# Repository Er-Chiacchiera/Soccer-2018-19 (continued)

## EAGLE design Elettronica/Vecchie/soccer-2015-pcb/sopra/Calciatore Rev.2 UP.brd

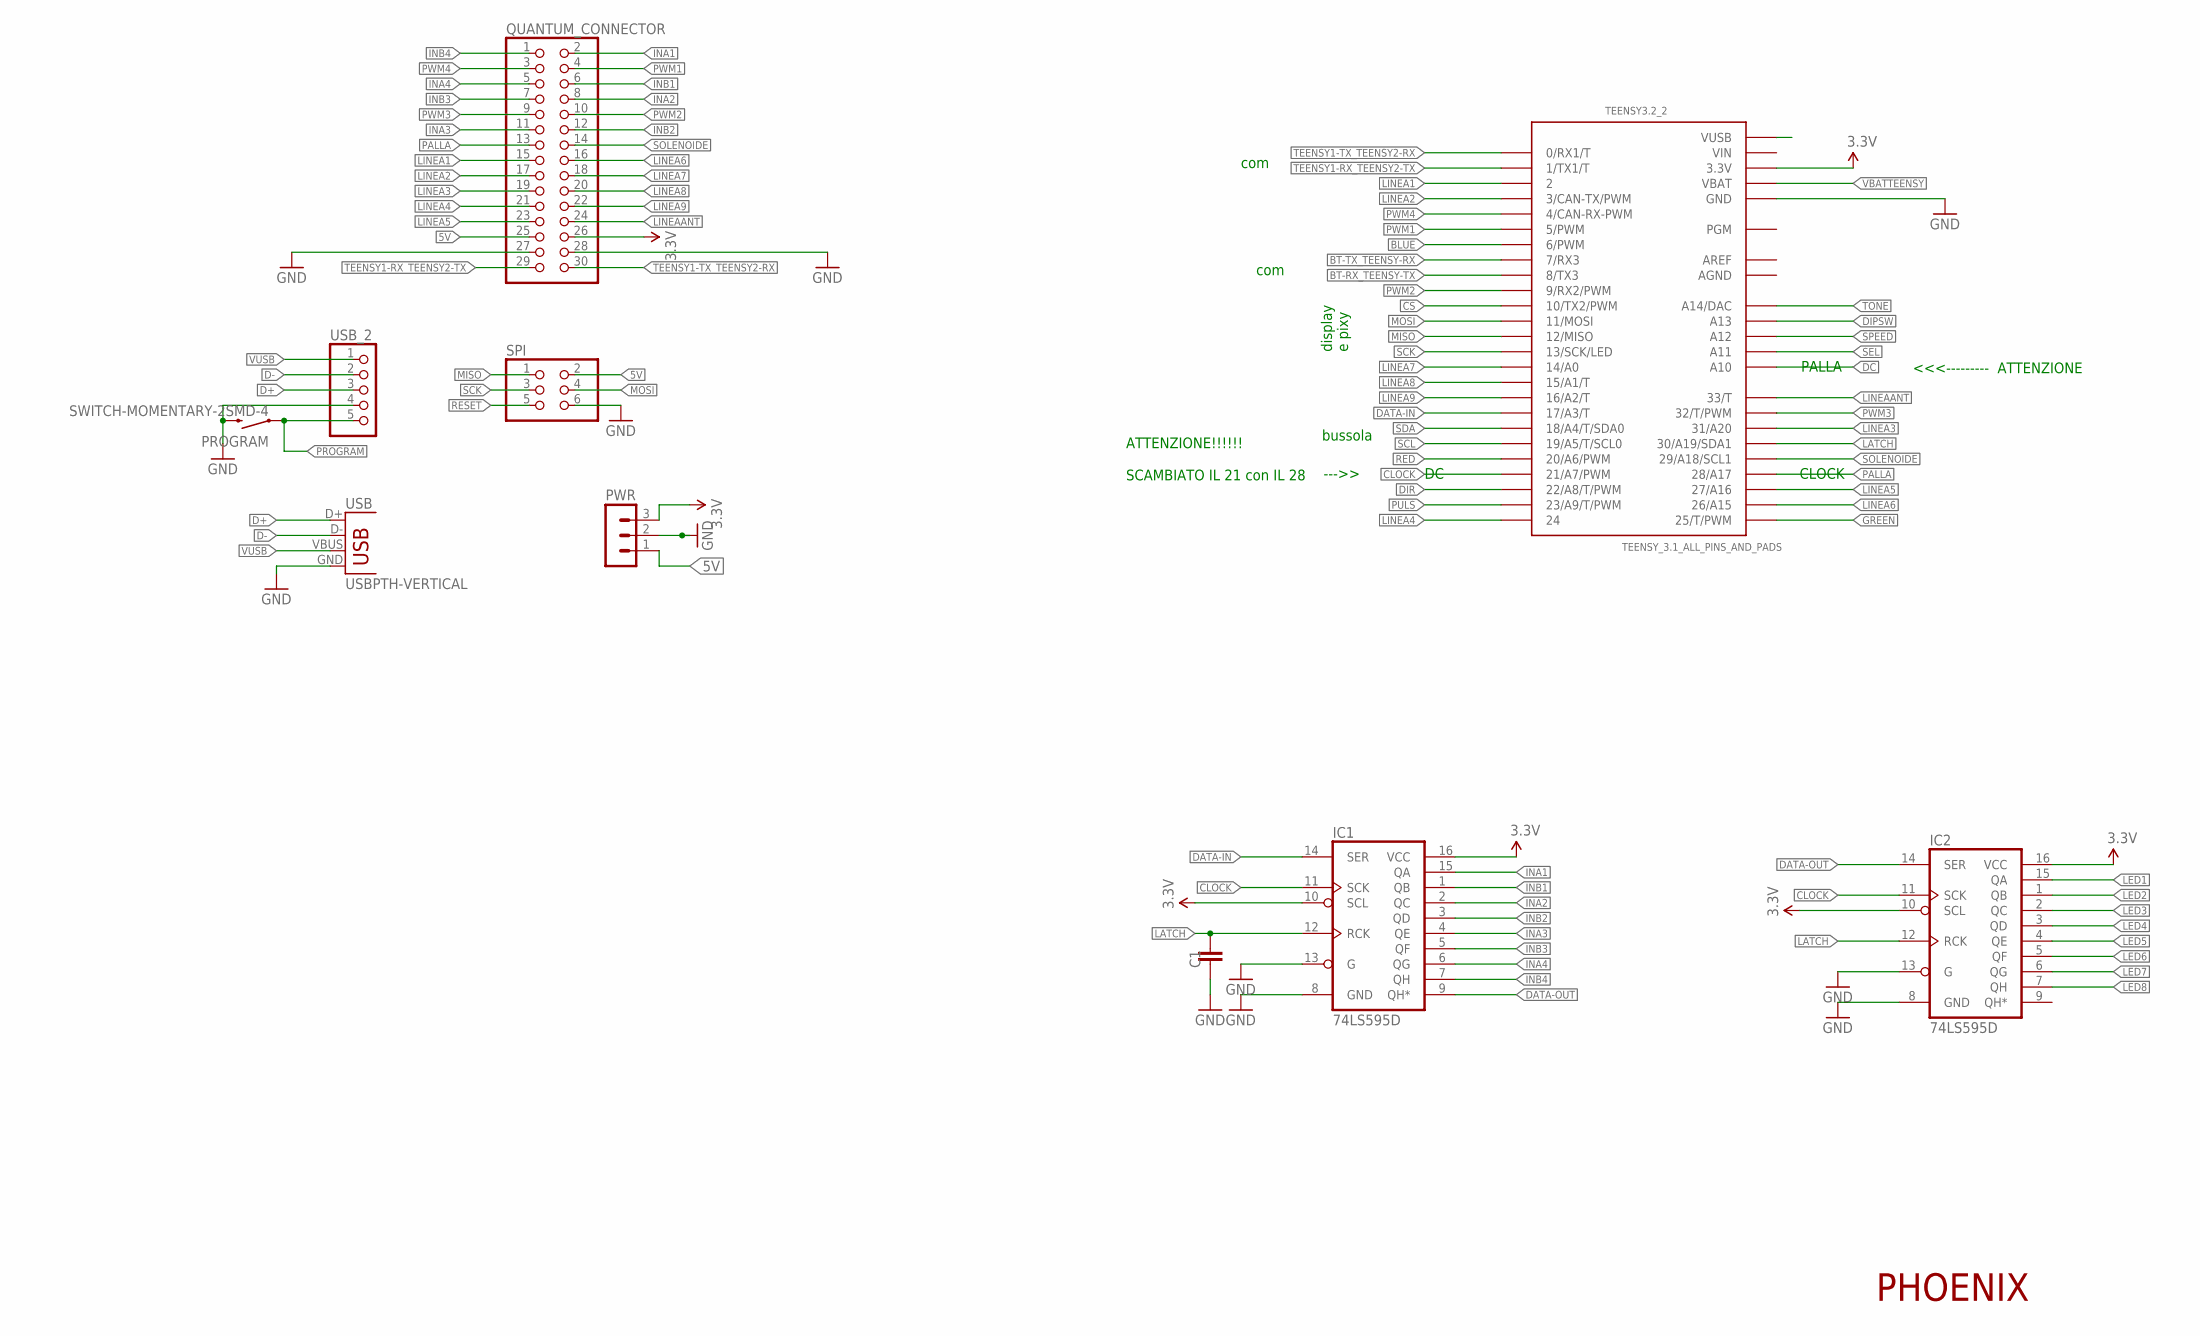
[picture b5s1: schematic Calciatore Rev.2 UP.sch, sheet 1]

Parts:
C1: C-EUC1206; C1206
IC1, IC2: 74LS595D; SO16
PROGRAM: SWITCH-MOMENTARY-2SMD-4; TACTILE_SWITCH_TALL
PWR: MA03-1
QUANTUM_CONNECTOR: PINHD-2X15; 2X15
SPI: PINHD-2X3; 2X03
TEENSY3.2_2: TEENSY_3.1_ALL_PINS_AND_PADS; TEENSY3_ALL_PINS_&_PADS
USB: USBPTH-VERTICAL; USB-B-PTH-VERTICAL
USB_2: PINHD-1X5; 1X05

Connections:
3.3V: IC1.10 (SCL), IC1.16 (VCC), IC2.10 (SCL), IC2.16 (VCC), PWR.3, QUANTUM_CONNECTOR.26, TEENSY3.2_2.3.3V, TEENSY3.2_2.3.3V1 (3.3V), TEENSY3.2_2.3.3V2 (3.3V); also elsewhere on the board
5V: PWR.1, QUANTUM_CONNECTOR.25, SPI.2; also elsewhere on the board
AGND: TEENSY3.2_2.AGND
AREF: TEENSY3.2_2.AREF
BLUE: TEENSY3.2_2.6 (6/PWM); also elsewhere on the board
BT-RX_TEENSY-TX: TEENSY3.2_2.8 (8/TX3); also elsewhere on the board
BT-TX_TEENSY-RX: TEENSY3.2_2.7 (7/RX3); also elsewhere on the board
CLOCK: IC1.11 (SCK), IC2.11 (SCK), TEENSY3.2_2.21/A7 (21/A7/PWM)
CS: TEENSY3.2_2.10 (10/TX2/PWM); also elsewhere on the board
D+: USB.D+, USB_2.3
D-: USB.D-, USB_2.2
DATA-IN: IC1.14 (SER), TEENSY3.2_2.17/A3 (17/A3/T)
DATA-OUT: IC1.9 (QH*), IC2.14 (SER)
DC: TEENSY3.2_2.A10; also elsewhere on the board
DIPSW: TEENSY3.2_2.A13; also elsewhere on the board
DIR: TEENSY3.2_2.22/A8 (22/A8/T/PWM); also elsewhere on the board
GND: C1.1, IC1.8 (GND), IC1.13 (G), IC2.8 (GND), IC2.13 (G), PROGRAM.B2 (2), PWR.2, QUANTUM_CONNECTOR.27, QUANTUM_CONNECTOR.28, SPI.6, TEENSY3.2_2.GND, TEENSY3.2_2.GND1 (GND), TEENSY3.2_2.GND2 (GND), USB.GND, USB_2.4; also elsewhere on the board
GREEN: TEENSY3.2_2.25 (25/T/PWM); also elsewhere on the board
INA1: IC1.15 (QA), QUANTUM_CONNECTOR.2
INA2: IC1.2 (QC), QUANTUM_CONNECTOR.8
INA3: IC1.4 (QE), QUANTUM_CONNECTOR.11
INA4: IC1.6 (QG), QUANTUM_CONNECTOR.5
INB1: IC1.1 (QB), QUANTUM_CONNECTOR.6
INB2: IC1.3 (QD), QUANTUM_CONNECTOR.12
INB3: IC1.5 (QF), QUANTUM_CONNECTOR.7
INB4: IC1.7 (QH), QUANTUM_CONNECTOR.1
LATCH: C1.2, IC1.12 (RCK), IC2.12 (RCK), TEENSY3.2_2.30 (30/A19/SDA1)
LED1: IC2.15 (QA); also elsewhere on the board
LED2: IC2.1 (QB); also elsewhere on the board
LED3: IC2.2 (QC); also elsewhere on the board
LED4: IC2.3 (QD); also elsewhere on the board
LED5: IC2.4 (QE); also elsewhere on the board
LED6: IC2.5 (QF); also elsewhere on the board
LED7: IC2.6 (QG); also elsewhere on the board
LED8: IC2.7 (QH); also elsewhere on the board
LINEA1: QUANTUM_CONNECTOR.15, TEENSY3.2_2.2
LINEA2: QUANTUM_CONNECTOR.17, TEENSY3.2_2.3 (3/CAN-TX/PWM)
LINEA3: QUANTUM_CONNECTOR.19, TEENSY3.2_2.31 (31/A20)
LINEA4: QUANTUM_CONNECTOR.21, TEENSY3.2_2.24
LINEA5: QUANTUM_CONNECTOR.23, TEENSY3.2_2.27 (27/A16)
LINEA6: QUANTUM_CONNECTOR.16, TEENSY3.2_2.26 (26/A15)
LINEA7: QUANTUM_CONNECTOR.18, TEENSY3.2_2.14/A0
LINEA8: QUANTUM_CONNECTOR.20, TEENSY3.2_2.15/A1 (15/A1/T)
LINEA9: QUANTUM_CONNECTOR.22, TEENSY3.2_2.16/A2 (16/A2/T)
LINEAANT: QUANTUM_CONNECTOR.24, TEENSY3.2_2.33 (33/T)
MISO: SPI.1, TEENSY3.2_2.12 (12/MISO)
MOSI: SPI.4, TEENSY3.2_2.11 (11/MOSI); also elsewhere on the board
PALLA: QUANTUM_CONNECTOR.13, TEENSY3.2_2.28 (28/A17)
PROGRAM: PROGRAM.A2 (1), USB_2.5
PULS: TEENSY3.2_2.23/A9 (23/A9/T/PWM); also elsewhere on the board
PWM1: QUANTUM_CONNECTOR.4, TEENSY3.2_2.5 (5/PWM)
PWM2: QUANTUM_CONNECTOR.10, TEENSY3.2_2.9 (9/RX2/PWM)
PWM3: QUANTUM_CONNECTOR.9, TEENSY3.2_2.32 (32/T/PWM)
PWM4: QUANTUM_CONNECTOR.3, TEENSY3.2_2.4 (4/CAN-RX-PWM)
RED: TEENSY3.2_2.20/A6 (20/A6/PWM); also elsewhere on the board
RESET: SPI.5
SCK: SPI.3, TEENSY3.2_2.13 (13/SCK/LED); also elsewhere on the board
SCL: TEENSY3.2_2.19/A5 (19/A5/T/SCL0); also elsewhere on the board
SDA: TEENSY3.2_2.18/A4 (18/A4/T/SDA0); also elsewhere on the board
SEL: TEENSY3.2_2.A11; also elsewhere on the board
SOLENOIDE: QUANTUM_CONNECTOR.14, TEENSY3.2_2.29 (29/A18/SCL1)
SPEED: TEENSY3.2_2.A12; also elsewhere on the board
TEENSY1-RX_TEENSY2-TX: QUANTUM_CONNECTOR.29, TEENSY3.2_2.1 (1/TX1/T)
TEENSY1-TX_TEENSY2-RX: QUANTUM_CONNECTOR.30, TEENSY3.2_2.0 (0/RX1/T)
TONE: TEENSY3.2_2.RESET/DAC (A14/DAC); also elsewhere on the board
VBATTEENSY: TEENSY3.2_2.VBAT
VIN: TEENSY3.2_2.VIN
VUSB: USB.VBUS, USB_2.1

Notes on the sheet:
PHOENIX
display e pixy
bussola
com
ATTENZIONE!!!!!! SCAMBIATO IL 21 con IL 28
--->>
<<<--------- ATTENZIONE
CLOCK
PALLA

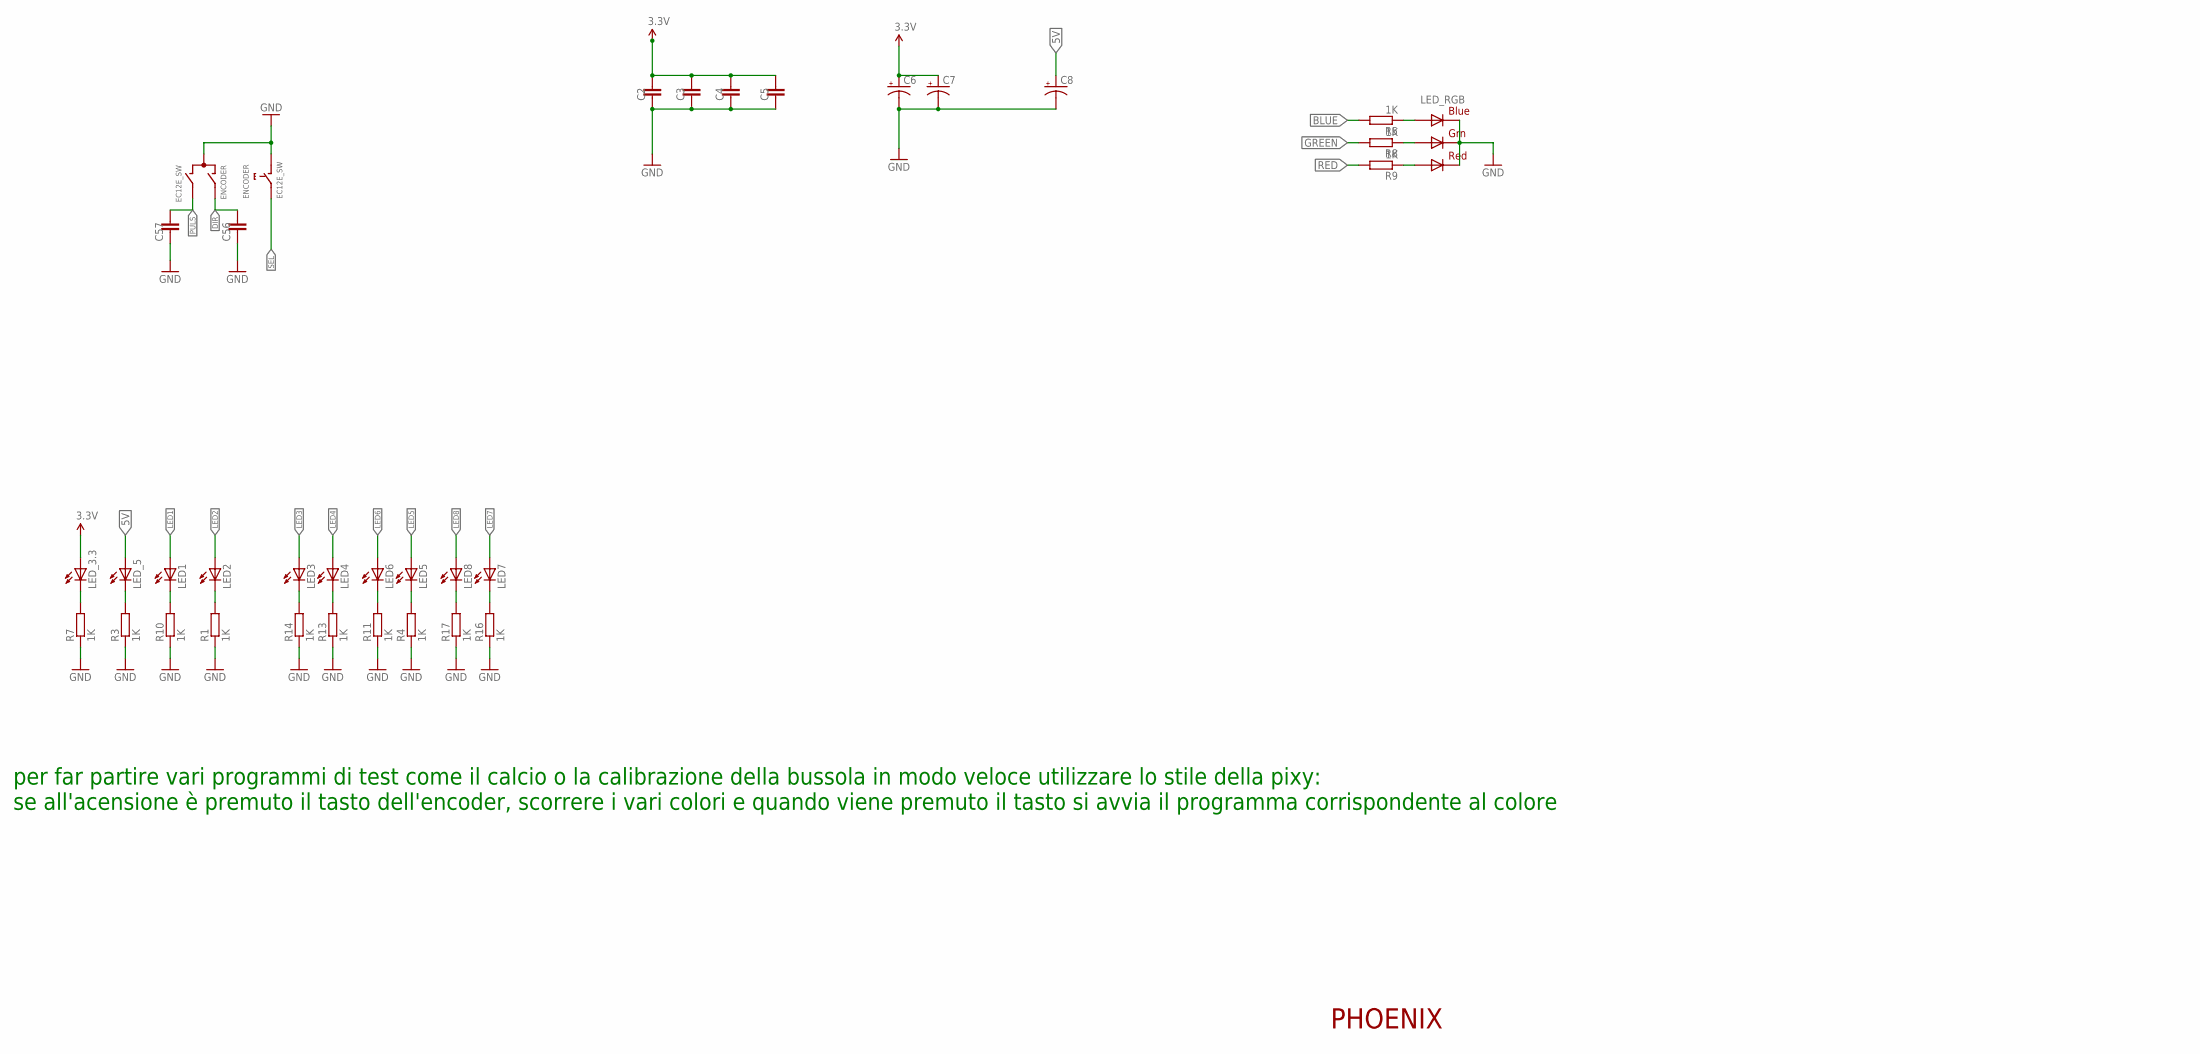
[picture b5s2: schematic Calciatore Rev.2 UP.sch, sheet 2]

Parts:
C2, C3, C4, C5, C56, C57: C-EUC1206; C1206
C6, C7, C8: CPOL-USE3.5-8; E3,5-8
ENCODER: EC12E_SW; ALPS_EC12E_SW
LED1, LED2, LED3, LED4, LED5, LED6, LED7, LED8: LEDSMT1206; 1206
LED_3.3, LED_5: LEDSMT1206; 1206
LED_RGB: RGBLED5050
R1, R3, R4, R5, R7, R8, R9, R10, R11, R13, R14, R16, R17: 1K; M1206

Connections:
3.3V: C2.2, C3.2, C4.2, C5.2, C6.+, C7.+, LED_3.3.A; also elsewhere on the board
5V: C8.+, LED_5.A; also elsewhere on the board
BLUE: R5.2; also elsewhere on the board
DIR: C56.2, ENCODER.A; also elsewhere on the board
GND: C2.1, C3.1, C4.1, C5.1, C6.-, C7.-, C8.-, C56.1, C57.1, ENCODER.C, ENCODER.D (1), LED_RGB.4 (BLUE_C), LED_RGB.5 (RED_C), LED_RGB.6 (GREEN_C), R1.1, R3.1, R4.1, R7.1, R10.1, R11.1, R13.1, R14.1, R16.1, R17.1; also elsewhere on the board
GREEN: R8.2; also elsewhere on the board
LED1: LED1.A; also elsewhere on the board
LED2: LED2.A; also elsewhere on the board
LED3: LED3.A; also elsewhere on the board
LED4: LED4.A; also elsewhere on the board
LED5: LED5.A; also elsewhere on the board
LED6: LED6.A; also elsewhere on the board
LED7: LED7.A; also elsewhere on the board
LED8: LED8.A; also elsewhere on the board
LED_3.3: LED_3.3.C, R7.2
unnamed: LED2.C, R1.2
unnamed: LED_5.C, R3.2
unnamed: LED5.C, R4.2
unnamed: LED6.C, R11.2
unnamed: LED7.C, R16.2
unnamed: LED_RGB.3 (BLUE_A), R5.1
unnamed: LED_RGB.1 (GREEN_A), R8.1
unnamed: LED_RGB.2 (RED_A), R9.1
unnamed: LED1.C, R10.2
unnamed: LED4.C, R13.2
unnamed: LED3.C, R14.2
unnamed: LED8.C, R17.2
PULS: C57.2, ENCODER.B; also elsewhere on the board
RED: R9.2; also elsewhere on the board
SEL: ENCODER.E (2); also elsewhere on the board

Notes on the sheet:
PHOENIX
per far partire vari programmi di test come il calcio o la calibrazione della bussola in modo veloce utilizzare lo stile della pixy: se all'acensione è premuto il tasto dell'encoder, scorrere i vari colori e quando viene premuto il tasto si avvia il programma corrispondente al colore

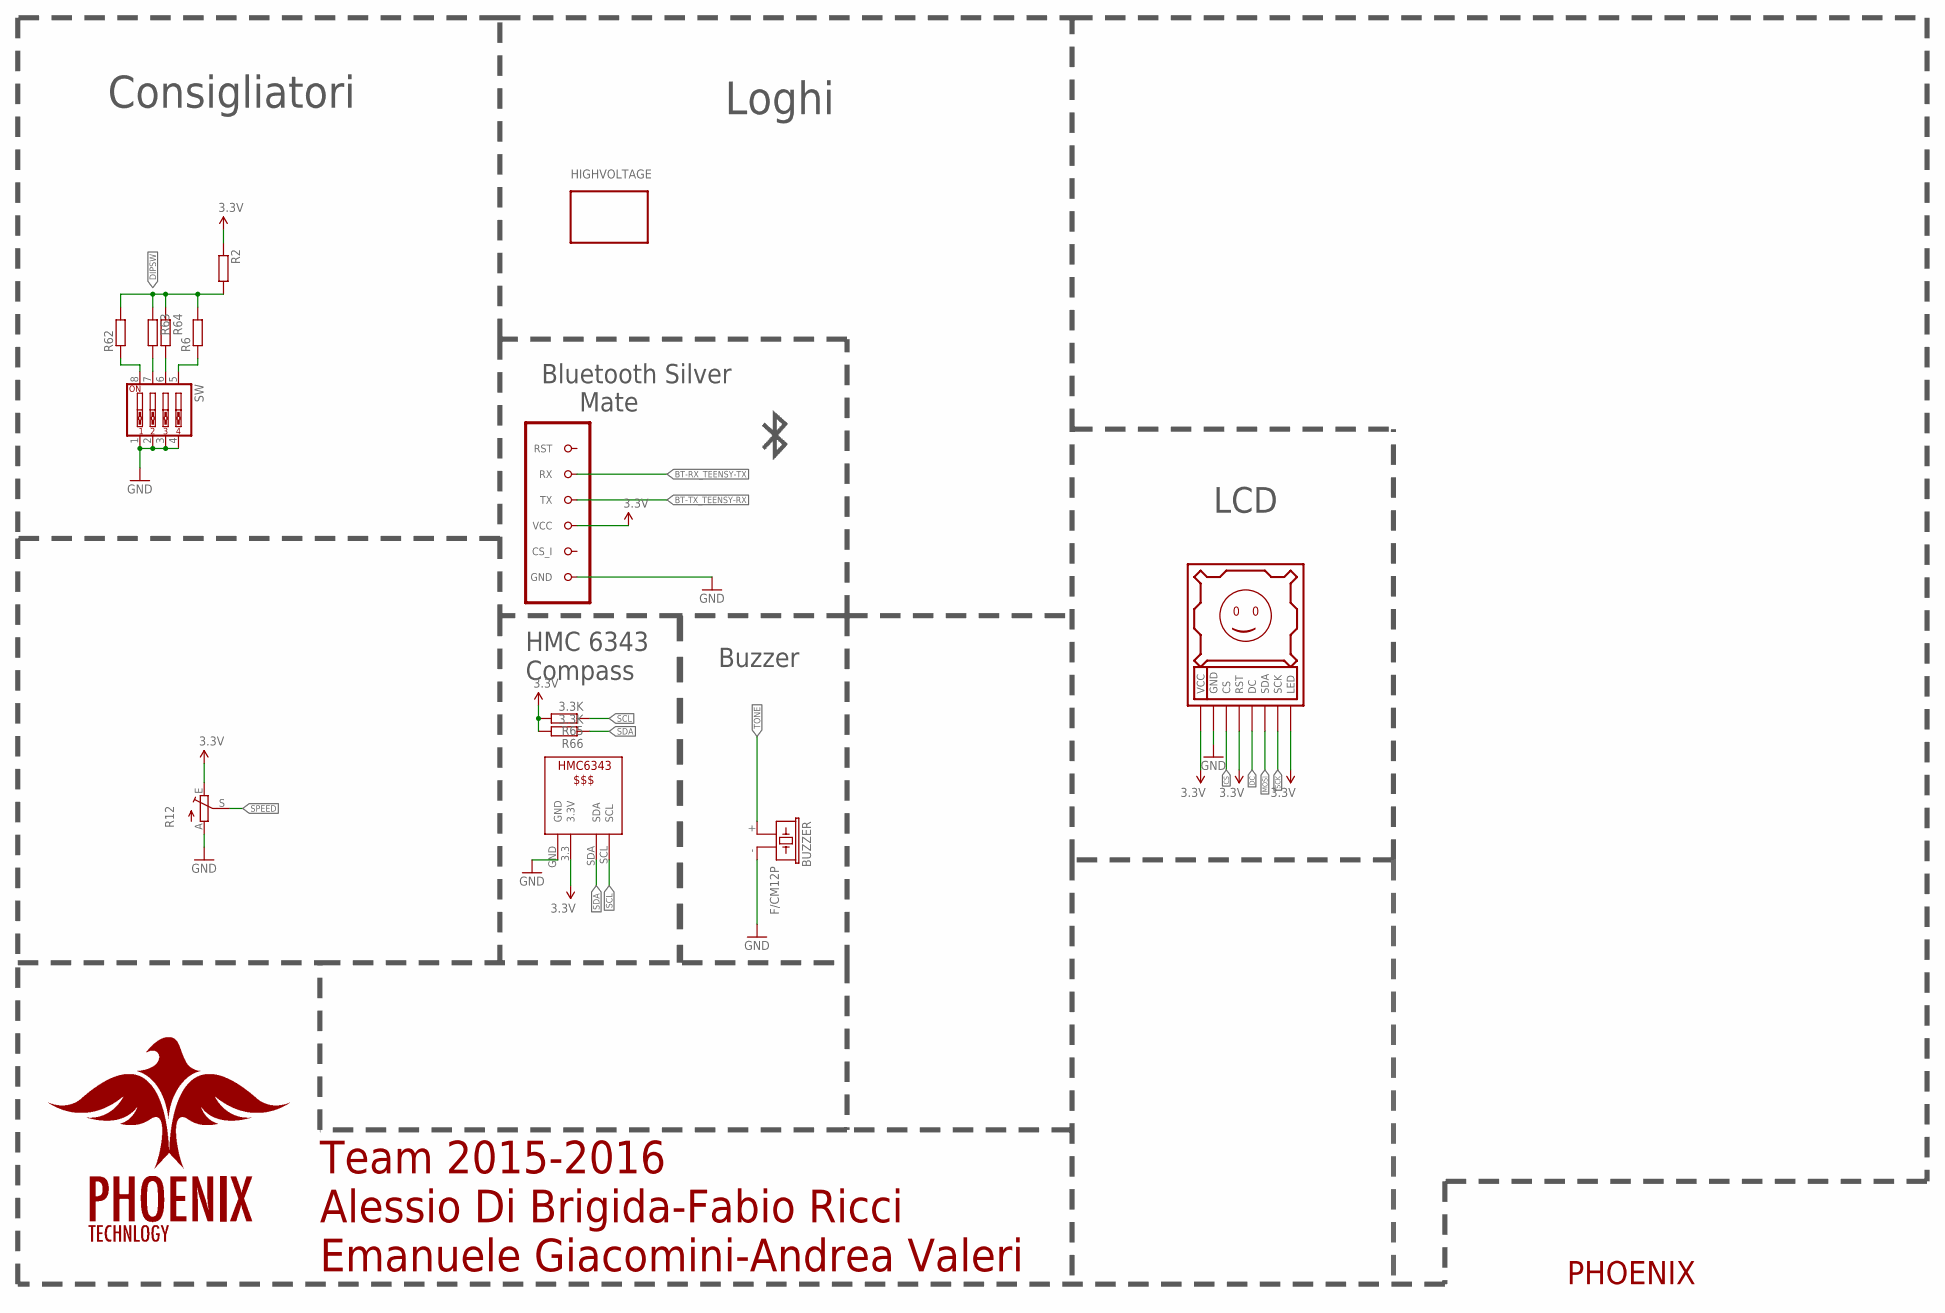
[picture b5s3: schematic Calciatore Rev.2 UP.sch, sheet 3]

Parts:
BUZZER: F/CM12P
DISPLAY1: DISPLAY128X128
HIGHVOLTAGE: LOGO; LOGOHV
R2, R6, R62, R63, R64: 10K; M1206
R12: TRIM_EU-S63P; S63P
R65, R66: 3.3K; M1206
SW: SW_DIP-4; EDG-04
U$5: HMC6343
U$9: BLUETOOTH

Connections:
3.3V: DISPLAY1.LED, DISPLAY1.RST, DISPLAY1.VCC, R2.1, R12.E, R65.2, R66.2, U$5.3.3 (3.3V), U$9.VCC; also elsewhere on the board
BT-RX_TEENSY-TX: U$9.RX; also elsewhere on the board
BT-TX_TEENSY-RX: U$9.TX; also elsewhere on the board
CS: DISPLAY1.CS; also elsewhere on the board
DC: DISPLAY1.DC; also elsewhere on the board
DIPSW: R2.2, R6.2, R62.2, R63.1, R64.1; also elsewhere on the board
GND: BUZZER.- (2), DISPLAY1.GND, R12.A, SW.1, SW.2, SW.3, SW.4, U$5.GND, U$9.GND; also elsewhere on the board
MOSI: DISPLAY1.SDA; also elsewhere on the board
unnamed: R64.2, SW.6
unnamed: R62.1, SW.8
unnamed: R6.1, SW.5
unnamed: R63.2, SW.7
SCK: DISPLAY1.SCK; also elsewhere on the board
SCL: R65.1, U$5.SCL; also elsewhere on the board
SDA: R66.1, U$5.SDA; also elsewhere on the board
SPEED: R12.S; also elsewhere on the board
TONE: BUZZER.+ (1); also elsewhere on the board

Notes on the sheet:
LCD
Buzzer
Bluetooth Silver Mate
HMC 6343 Compass
Consigliatori
Loghi
Team 2015-2016 Alessio Di Brigida-Fabio Ricci Emanuele Giacomini-Andrea Valeri
PHOENIX

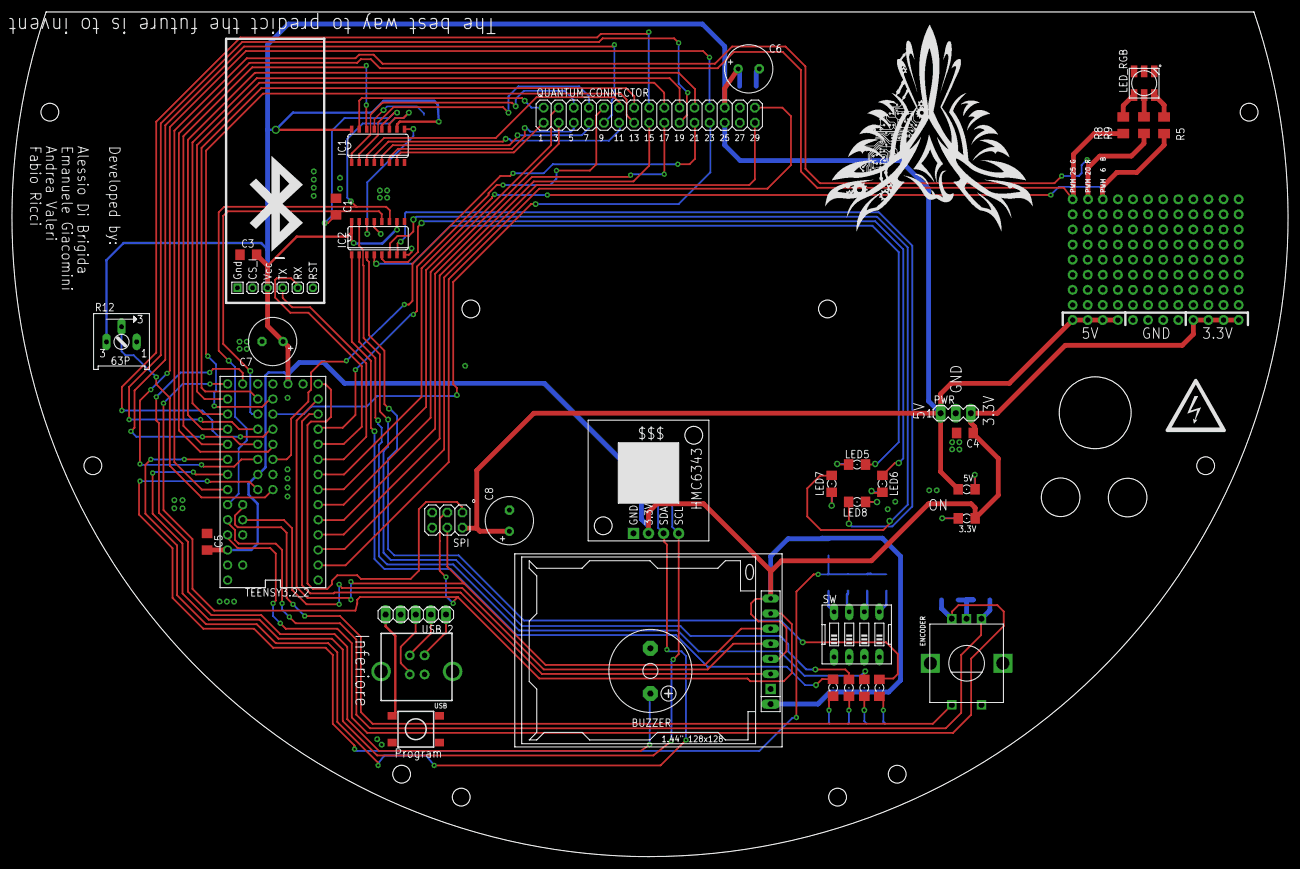
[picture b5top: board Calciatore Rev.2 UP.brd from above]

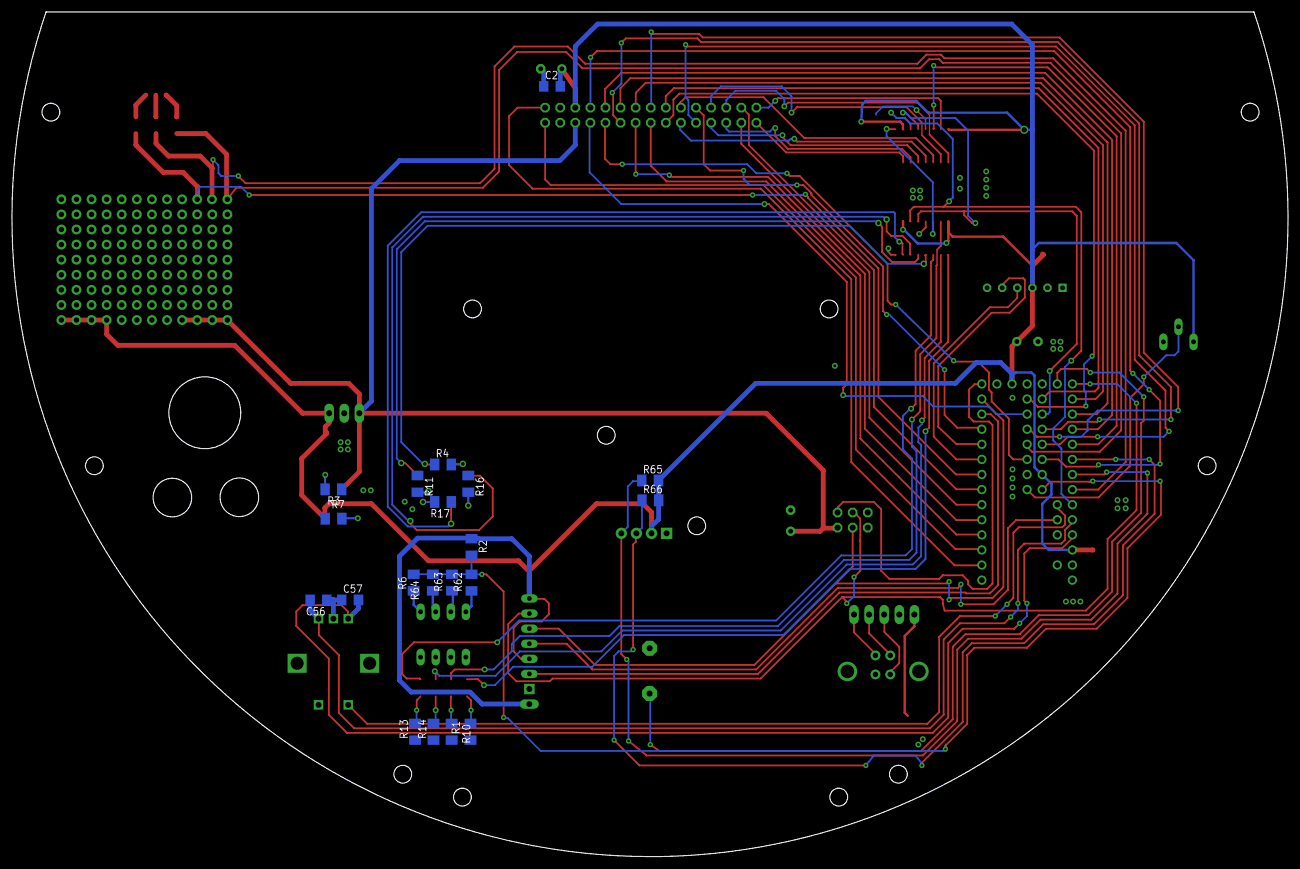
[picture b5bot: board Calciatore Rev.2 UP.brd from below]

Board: 2 copper layers, 214.8 x 142.2 mm, 59 parts (20 on the bottom side), 80 nets.

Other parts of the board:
U$1: PHOENIX

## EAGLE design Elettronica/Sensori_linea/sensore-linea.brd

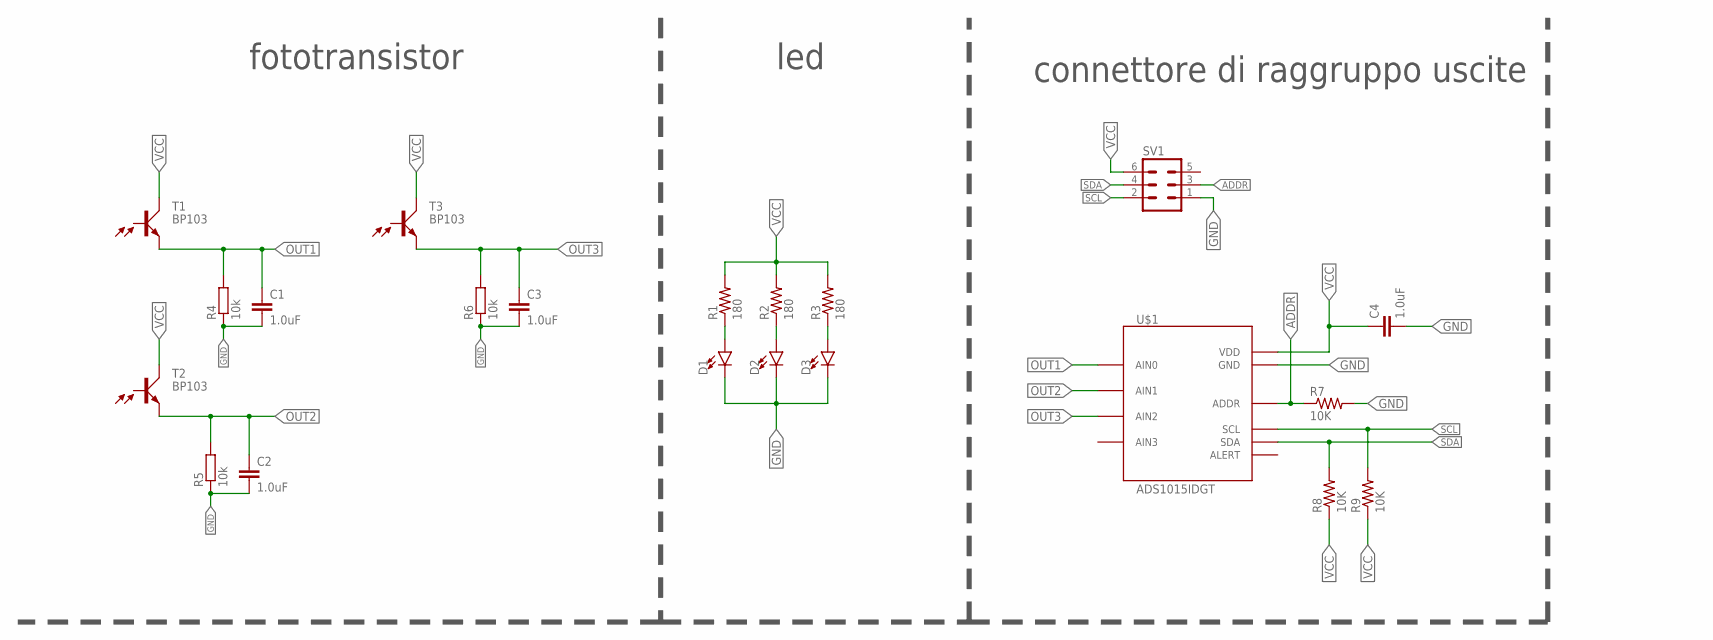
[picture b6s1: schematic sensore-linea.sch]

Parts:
C1, C2, C3: 1.0uF; 1206
C4: 1.0uF; 0402
D1, D2, D3: LED3MM; LED_3MM
R1, R2, R3: 180; 0204/7
R4, R5, R6: 10k; R1206
R7, R8, R9: 10K; 0204/7
SV1: MA03-2
T1, T2, T3: BP103
U$1: ADS1015IDGT; MSOP10_0.5

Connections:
ADDR: R7.1, SV1.3, U$1.1 (ADDR)
GND: C1.2, C2.2, C3.2, C4.2, D1.K (C), D2.K (C), D3.K (C), R4.1, R5.1, R6.1, R7.2, SV1.1, U$1.3 (GND)
unnamed: D1.A, R1.1
unnamed: D2.A, R2.1
unnamed: D3.A, R3.1
OUT1: C1.1, R4.2, T1.E, U$1.4 (AIN0)
OUT2: C2.1, R5.2, T2.E, U$1.5 (AIN1)
OUT3: C3.1, R6.2, T3.E, U$1.6 (AIN2)
SCL: R9.2, SV1.2, U$1.10 (SCL)
SDA: R8.2, SV1.4, U$1.9 (SDA)
VCC: C4.1, R1.2, R2.2, R3.2, R8.1, R9.1, SV1.6, T1.C, T2.C, T3.C, U$1.8 (VDD)

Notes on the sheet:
fototransistor
led
connettore di raggruppo uscite

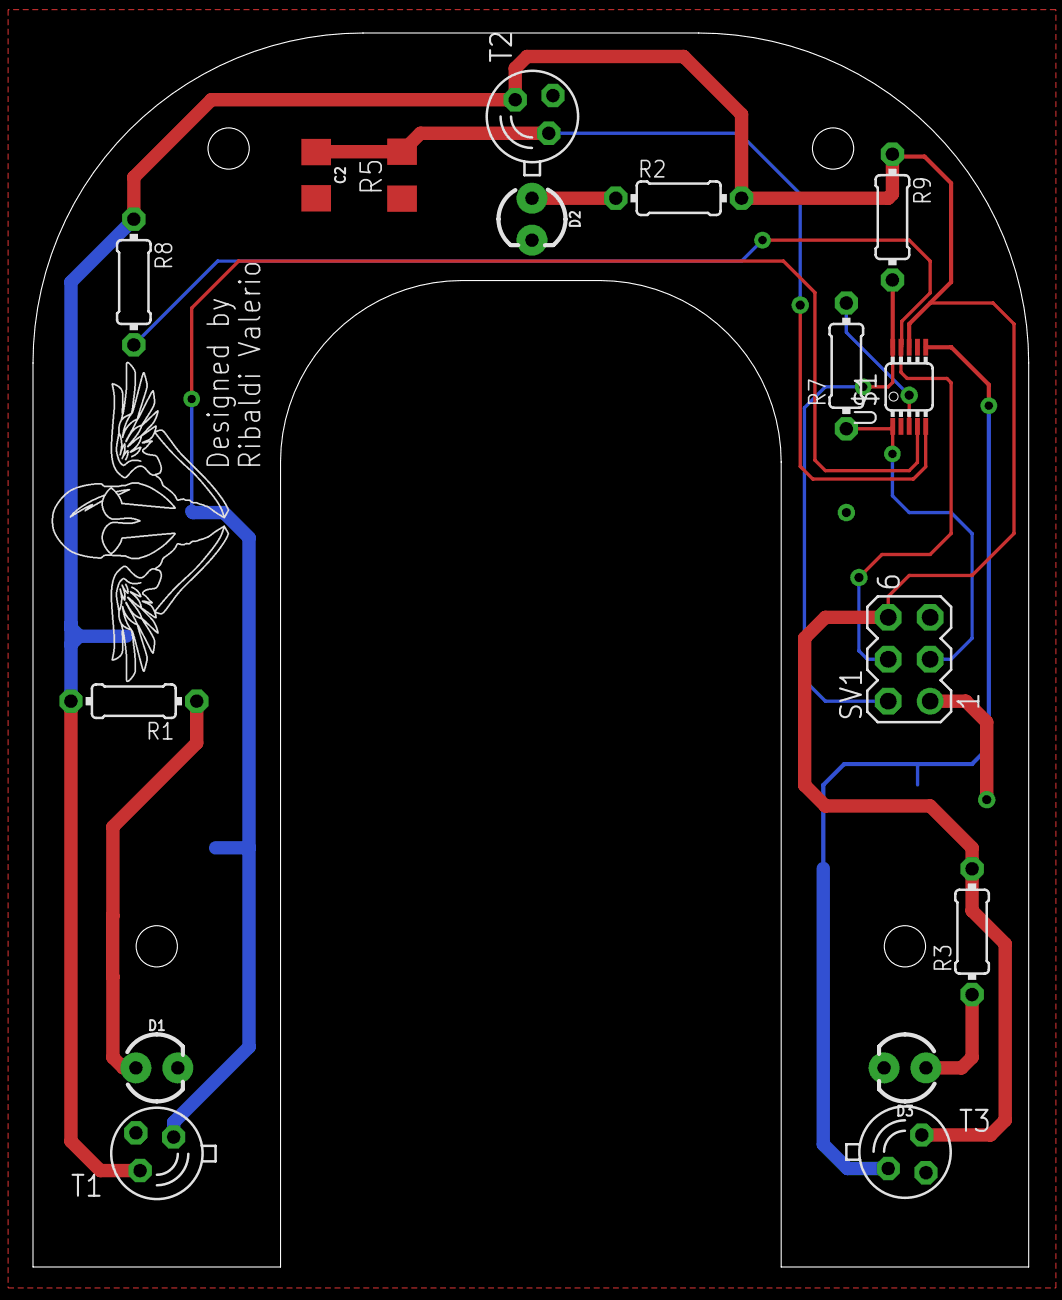
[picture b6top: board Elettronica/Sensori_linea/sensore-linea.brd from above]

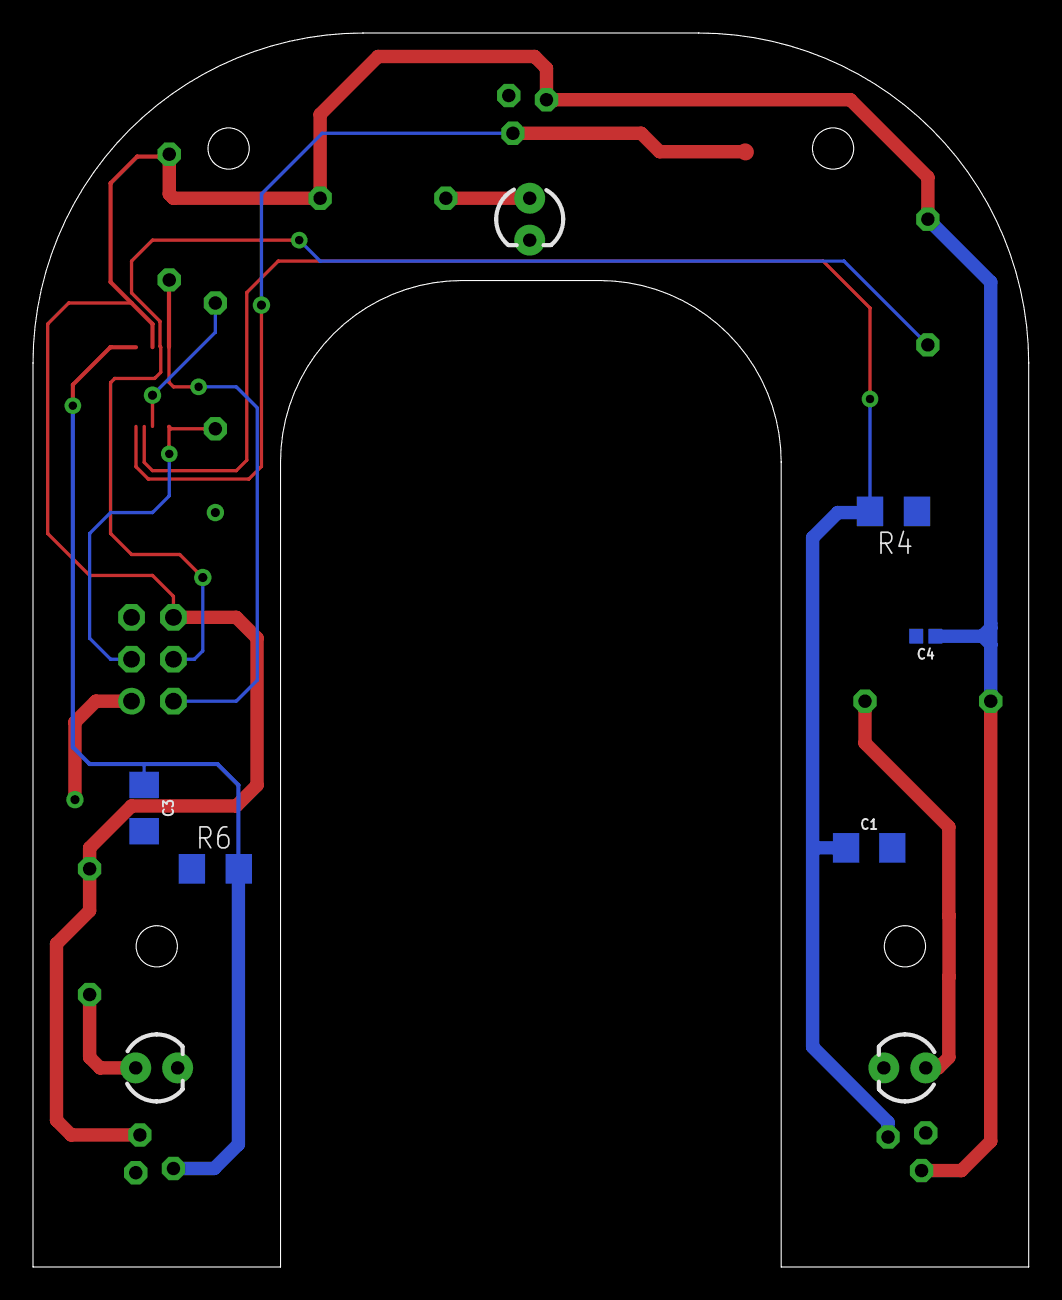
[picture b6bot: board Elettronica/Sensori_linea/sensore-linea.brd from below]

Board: 2 copper layers, 60.3 x 74.8 mm, 21 parts (5 on the bottom side), 11 nets.

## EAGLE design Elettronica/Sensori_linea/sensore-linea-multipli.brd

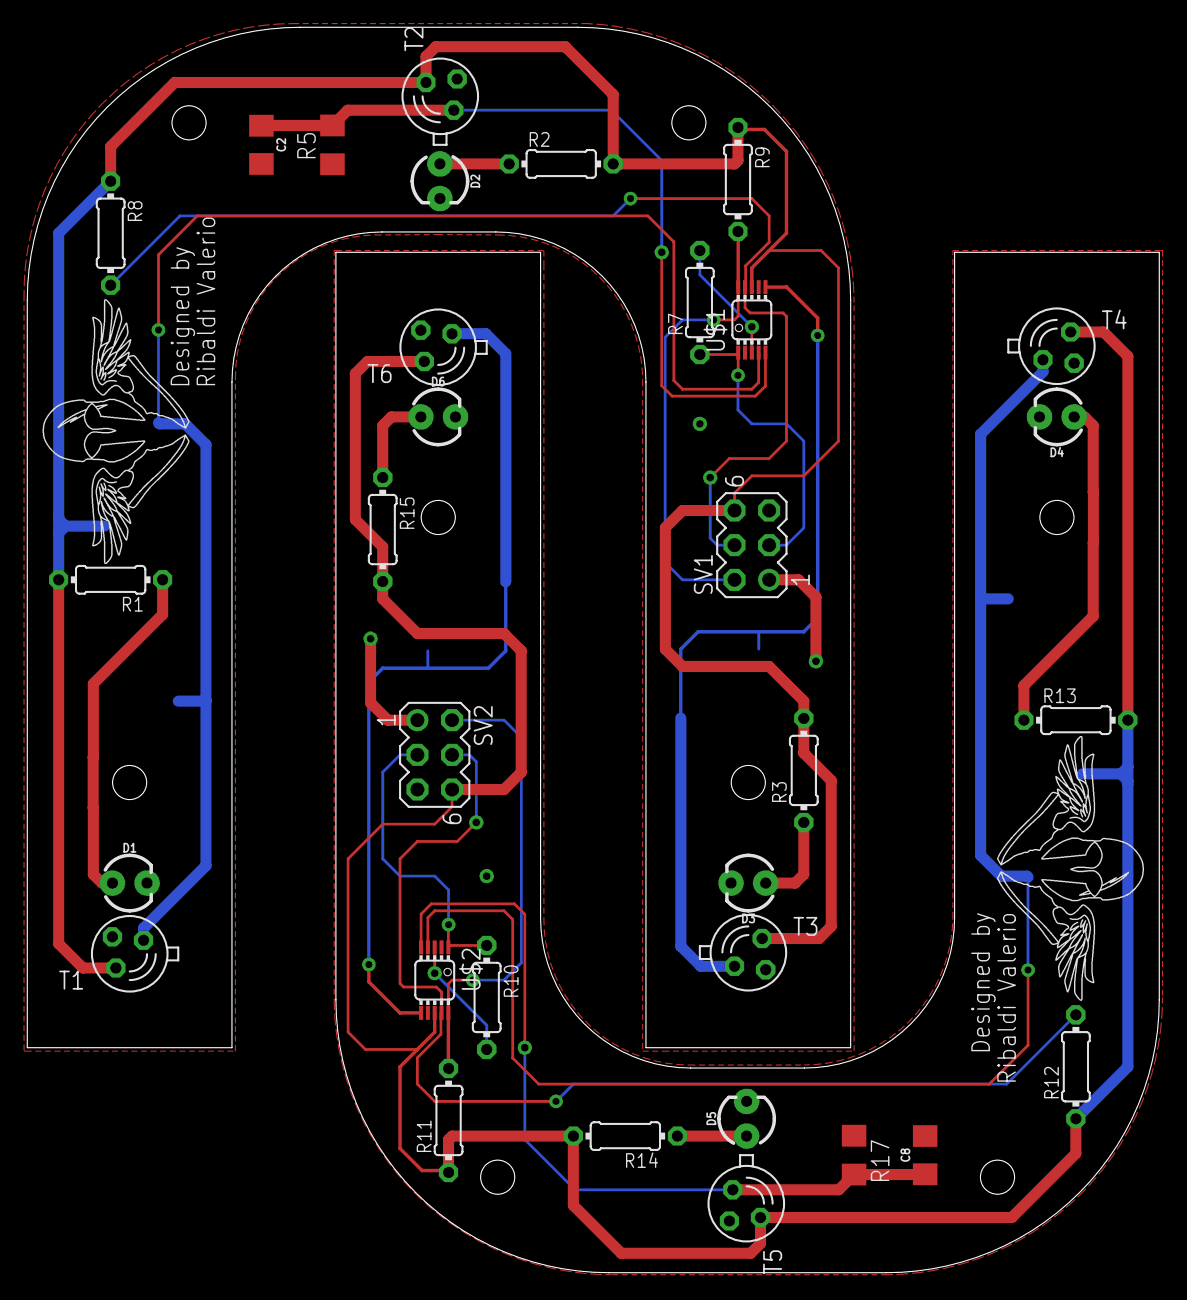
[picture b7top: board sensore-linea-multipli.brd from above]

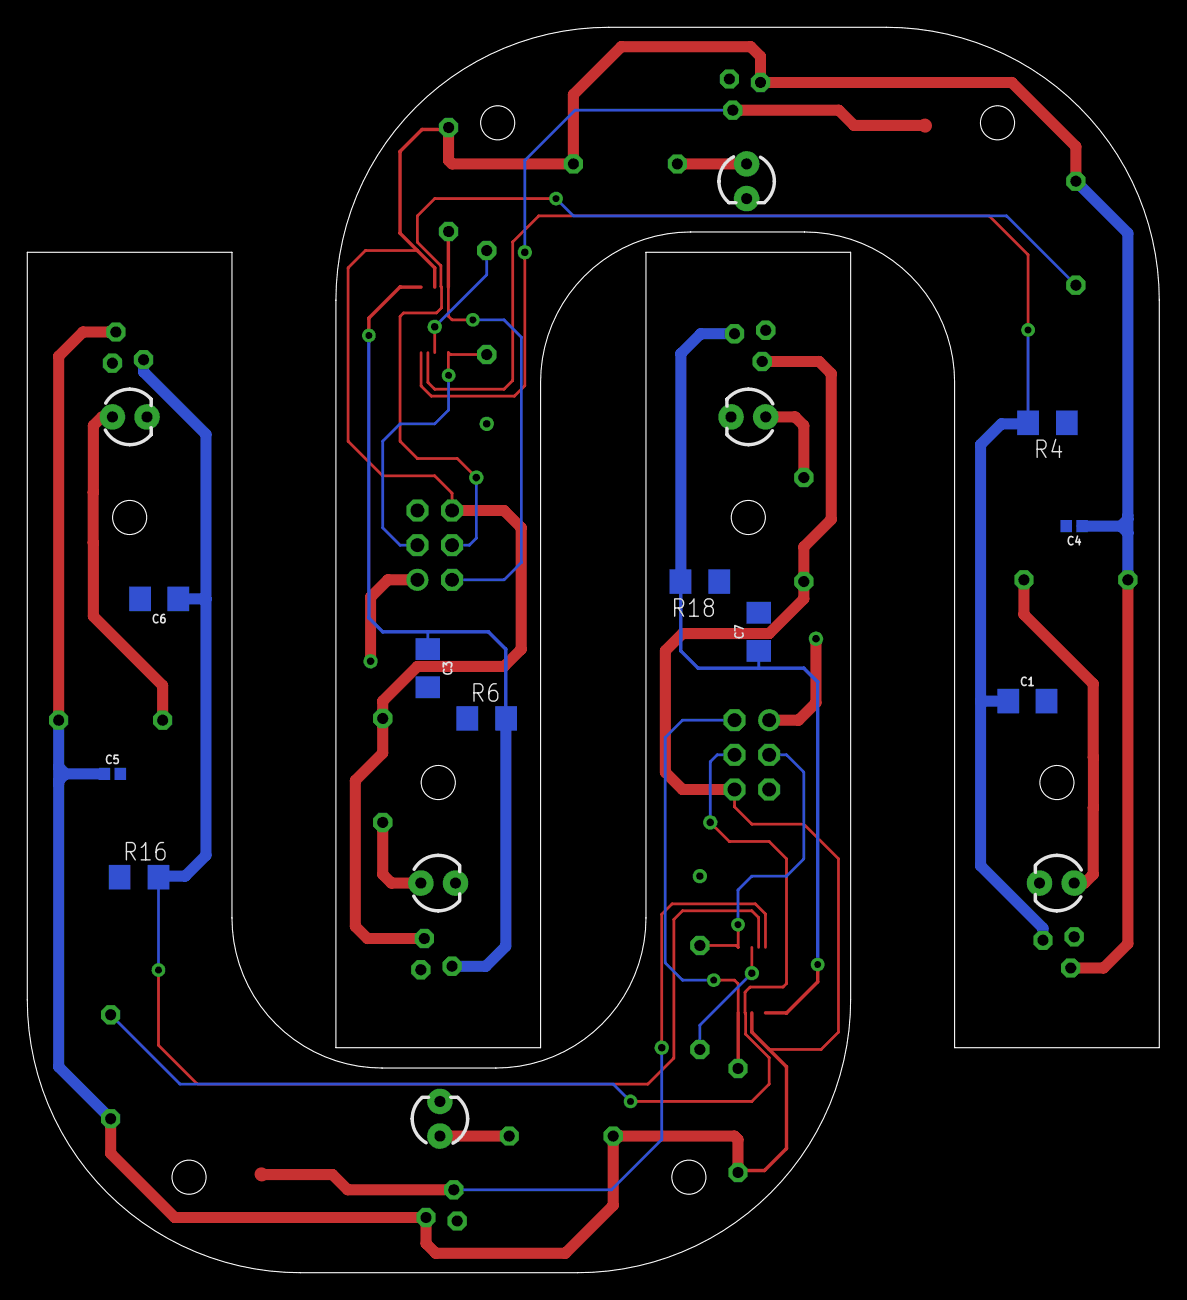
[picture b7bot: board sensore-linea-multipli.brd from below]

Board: 2 copper layers, 83.0 x 91.3 mm, 42 parts (10 on the bottom side), 22 nets.

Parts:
C1, C2, C3, C6, C7, C8: 1.0uF; 1206
C4, C5: 1.0uF; 0402
D1, D2, D3, D4, D5, D6: LED_3MM
R1, R2, R3, R13, R14, R15: 180; 0204/7
R4, R5, R6, R16, R17, R18: 10k; R1206
R7, R8, R9, R10, R11, R12: 10K; 0204/7
SV1, SV2: MA03-2
T1, T2, T3, T4, T5, T6: BP103
U$1, U$2: ADS1015IDGT; MSOP10_0.5

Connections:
ADDR: R7.1, SV1.3, U$1.1
ADDR1: R10.1, SV2.3, U$2.1
GND: C1.2, C2.2, C3.2, C4.2, D1.K, D2.K, D3.K, R4.1, R5.1, R6.1, R7.2, SV1.1, U$1.3
GND1: C5.2, C6.2, C7.2, C8.2, D4.K, D5.K, D6.K, R10.2, R16.1, R17.1, R18.1, SV2.1, U$2.3
unnamed: D4.A, R13.1
unnamed: D1.A, R1.1
unnamed: D2.A, R2.1
unnamed: D3.A, R3.1
unnamed: D5.A, R14.1
unnamed: D6.A, R15.1
OUT1: C1.1, R4.2, T1.E, U$1.4
OUT2: C2.1, R5.2, T2.E, U$1.5
OUT3: C3.1, R6.2, T3.E, U$1.6
OUT4: C6.1, R16.2, T4.E, U$2.4
OUT5: C8.1, R17.2, T5.E, U$2.5
OUT6: C7.1, R18.2, T6.E, U$2.6
SCL: R9.2, SV1.2, U$1.10
SCL1: R11.2, SV2.2, U$2.10
SDA: R8.2, SV1.4, U$1.9
SDA1: R12.2, SV2.4, U$2.9
VCC: C4.1, R1.2, R2.2, R3.2, R8.1, R9.1, SV1.6, T1.C, T2.C, T3.C, U$1.8
VCC1: C5.1, R11.1, R12.1, R13.2, R14.2, R15.2, SV2.6, T4.C, T5.C, T6.C, U$2.8
